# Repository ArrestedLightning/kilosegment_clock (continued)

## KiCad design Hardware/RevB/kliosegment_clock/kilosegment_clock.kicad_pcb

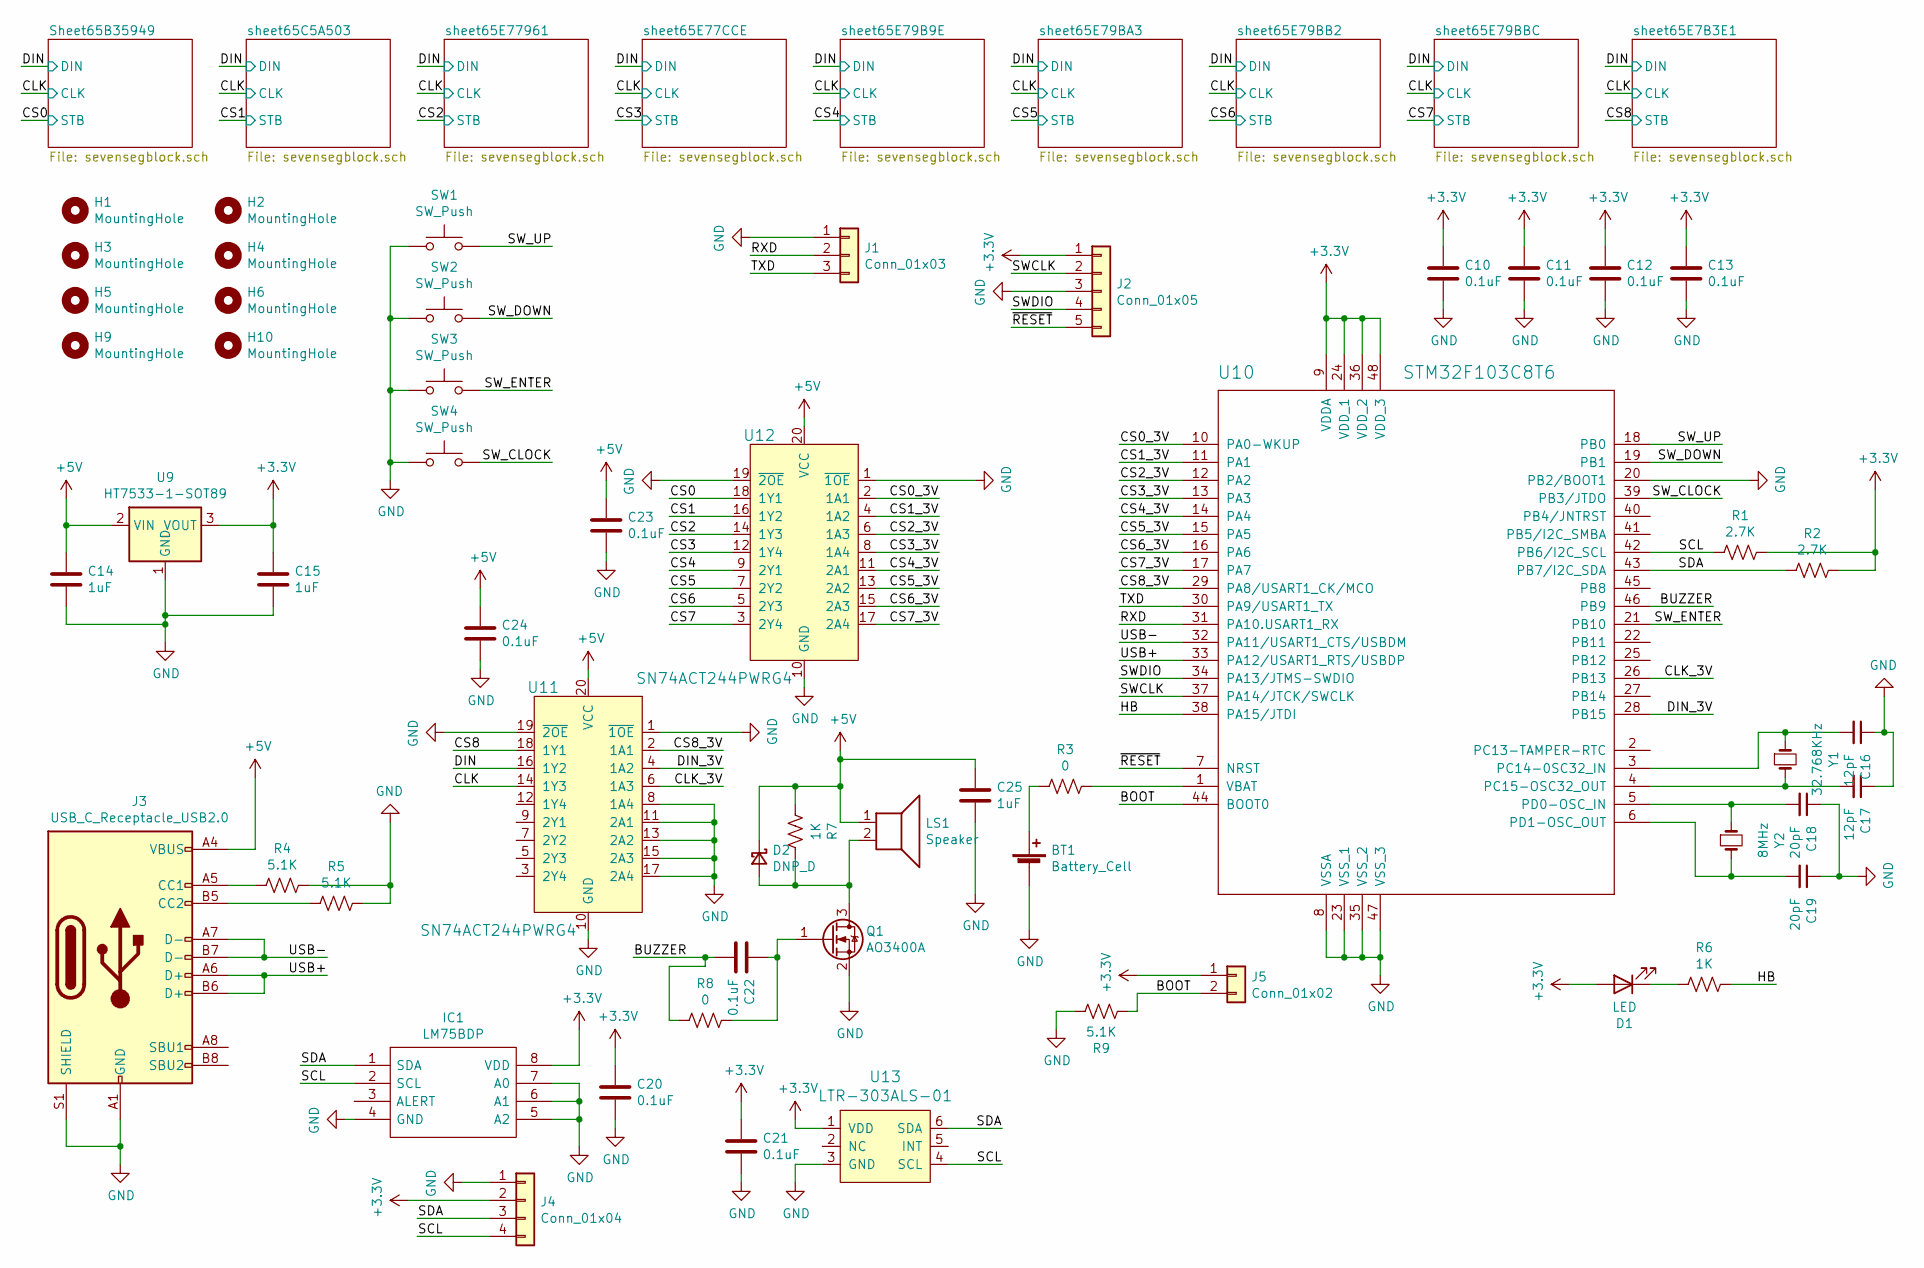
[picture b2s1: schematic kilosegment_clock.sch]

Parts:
BT1: Battery_Cell; BatteryHolder_CR2032-BS-6-1_1x2032; Digikey BH-49A-5-T-BK
C10, C11, C12, C13, C20, C21, C22, C23, C24: 0.1uF; C_0805_2012Metric_Pad1.18x1.45mm_HandSolder; Digikey 1276-1003-1-ND
C14, C15, C25: 1uF; C_0805_2012Metric_Pad1.18x1.45mm_HandSolder; Digikey 1276-1026-1-ND
C16, C17: 12pF; C_0805_2012Metric_Pad1.18x1.45mm_HandSolder; Digikey CML0805C0G120JT50V
C18, C19: 20pF; C_0805_2012Metric_Pad1.18x1.45mm_HandSolder; Digikey 738-CML0805C0G200JT50VCT-ND
D1: LED; LED_0805_2012Metric_Pad1.15x1.40mm_HandSolder; Digikey 754-1132-1-ND
D2: DNP_D; D_SOD-123
H1, H2, H3, H4, H5, H6, H9, H10: MountingHole; pcb_nut_m3
IC1: LM75BDP; MSOP-8_3x3mm_P0.65mm; Digikey 568-4768-1-ND
J1: Conn_01x03; PinHeader_1x03_P2.54mm_Vertical
J2: Conn_01x05; PinHeader_1x05_P2.54mm_Vertical
J3: USB_C_Receptacle_USB2.0; USB_C_Receptacle_HRO_TYPE-C-31-M-12; Digikey 664-12402012E212ACT-ND
J4: Conn_01x04; PinHeader_1x04_P2.54mm_Vertical
J5: Conn_01x02; PinHeader_1x02_P2.54mm_Vertical
LS1: Speaker; BUZ-TH_PKM13EPYH4002-B0; Digikey 490-4697-ND
Q1: AO3400A; SOT-23_Handsoldering; LCSC Part C20917
R1, R2: 2.7K; R_0805_2012Metric_Pad1.20x1.40mm_HandSolder; Digikey RMCF0805FT2K70CT-ND
R3, R8: 0; R_0805_2012Metric_Pad1.20x1.40mm_HandSolder; Digikey RMCF0805ZT0R00CT-ND
R4, R5, R9: 5.1K; R_0805_2012Metric_Pad1.20x1.40mm_HandSolder; Digikey RMCF0805FT5K10CT-ND
R6, R7: 1K; R_0805_2012Metric_Pad1.20x1.40mm_HandSolder; Digikey RMCF0805FT1K00CT-ND
SW1, SW2, SW3, SW4: SW_Push; SW_SPST_TL3342; Digikey CKN12222-1-ND
U9: HT7533-1-SOT89; SOT-89-3; Digikey 2129-RH5RL33AA-T1-FECT-ND
U10: STM32F103C8T6; LQFP-48_7x7mm_P0.5mm; Digikey 497-11517-ND
U11, U12: SN74ACT244PWRG4; TSSOP-20_4.4x6.5mm_P0.65mm; LCSC Part C6930
U13: LTR-303ALS-01; SOT-363_SC-70-6_Handsoldering; LCSC Part C364577
Y1: 32.768KHz; Crystal_SMD_3215-2Pin_3.2x1.5mm; Digikey 9H03200031-ND
Y2: 8MHz; Crystal_SMD_5032-2Pin_5.0x3.2mm_HandSoldering; Digikey XC2103CT-ND

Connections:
+3V3: C10.1, C11.1, C12.1, C13.1, C15.1, C20.1, C21.1, D1.2 (A), IC1.8 (VDD), J2.1, J4.2, J5.1, R1.1, R2.1, U9.3 (VOUT), U10.9 (VDDA), U10.24 (VDD_1), U10.36 (VDD_2), U10.48 (VDD_3), U13.1 (VDD)
+5V: C14.1, C23.1, C24.1, C25.1, D2.1 (K), J3.A4 (VBUS), J3.A9 (VBUS), J3.B4 (VBUS), J3.B9 (VBUS), LS1.1, R7.2, U9.2 (VIN), U11.20 (VCC), U12.20 (VCC); also elsewhere on the board
/BOOT: J5.2, R9.2, U10.44 (BOOT0)
/BUZZER: C22.2, R8.2, U10.46 (PB9)
/CLK: U11.14 (1Y3); also elsewhere on the board
/CLK_3V: U10.26 (PB13), U11.6 (1A3)
/CS0: U12.18 (1Y1); also elsewhere on the board
/CS0_3V: U10.10 (PA0-WKUP), U12.2 (1A1)
/CS1: U12.16 (1Y2); also elsewhere on the board
/CS1_3V: U10.11 (PA1), U12.4 (1A2)
/CS2: U12.14 (1Y3); also elsewhere on the board
/CS2_3V: U10.12 (PA2), U12.6 (1A3)
/CS3: U12.12 (1Y4); also elsewhere on the board
/CS3_3V: U10.13 (PA3), U12.8 (1A4)
/CS4: U12.9 (2Y1); also elsewhere on the board
/CS4_3V: U10.14 (PA4), U12.11 (2A1)
/CS5: U12.7 (2Y2); also elsewhere on the board
/CS5_3V: U10.15 (PA5), U12.13 (2A2)
/CS6: U12.5 (2Y3); also elsewhere on the board
/CS6_3V: U10.16 (PA6), U12.15 (2A3)
/CS7: U12.3 (2Y4); also elsewhere on the board
/CS7_3V: U10.17 (PA7), U12.17 (2A4)
/CS8: U11.18 (1Y1); also elsewhere on the board
/CS8_3V: U10.29 (PA8/USART1_CK/MCO), U11.2 (1A1)
/DIN: U11.16 (1Y2); also elsewhere on the board
/DIN_3V: U10.28 (PB15), U11.4 (1A2)
/HB: R6.1, U10.38 (PA15/JTDI)
/RXD: J1.2, U10.31 (PA10.USART1_RX)
/SCL: IC1.2 (SCL), J4.4, R1.2, U10.42 (PB6/I2C_SCL), U13.4 (SCL)
/SDA: IC1.1 (SDA), J4.3, R2.2, U10.43 (PB7/I2C_SDA), U13.6 (SDA)
/SWCLK: J2.2, U10.37 (PA14/JTCK/SWCLK)
/SWDIO: J2.4, U10.34 (PA13/JTMS-SWDIO)
/SW_CLOCK: SW4.2, U10.39 (PB3/JTDO)
/SW_DOWN: SW2.2, U10.19 (PB1)
/SW_ENTER: SW3.2, U10.21 (PB10)
/SW_UP: SW1.2, U10.18 (PB0)
/TXD: J1.3, U10.30 (PA9/USART1_TX)
/USB+: J3.A6 (D+), J3.B6 (D+), U10.33 (PA12/USART1_RTS/USBDP)
/USB-: J3.A7 (D-), J3.B7 (D-), U10.32 (PA11/USART1_CTS/USBDM)
/~RESET: J2.5, U10.7 (NRST)
GND: BT1.2 (-), C10.2, C11.2, C12.2, C13.2, C14.2, C15.2, C16.1, C17.1, C18.1, C19.1, C20.2, C21.2, C23.2, C24.2, C25.2, IC1.4 (GND), IC1.5 (A2), IC1.6 (A1), IC1.7 (A0), J1.1, J2.3, J3.A1 (GND), J3.A12 (GND), J3.B1 (GND), J3.B12 (GND), J3.S1 (SHIELD), J4.1, Q1.2 (S), R4.1, R5.1, R9.1, SW1.1, SW2.1, SW3.1, SW4.1, U9.1 (GND), U10.8 (VSSA), U10.20 (PB2/BOOT1), U10.23 (VSS_1), U10.35 (VSS_2), U10.47 (VSS_3), U11.1 (~1OE), U11.8 (1A4), U11.10 (GND), U11.11 (2A1), U11.13 (2A2), U11.15 (2A3), U11.17 (2A4), U11.19 (~2OE), U12.1 (~1OE), U12.10 (GND), U12.19 (~2OE), U13.3 (GND); also elsewhere on the board
unnamed: BT1.1 (+), R3.2
unnamed: C16.2, U10.3 (PC14-0SC32_IN), Y1.1
unnamed: C17.2, U10.4 (PC15-OSC32_OUT), Y1.2
unnamed: C18.2, U10.5 (PD0-OSC_IN), Y2.1
unnamed: C19.2, U10.6 (PD1-OSC_OUT), Y2.2
unnamed: C22.1, Q1.1 (G), R8.1
unnamed: D1.1 (K), R6.2
unnamed: D2.2 (A), LS1.2, Q1.3 (D), R7.1
unnamed: J3.A5 (CC1), R4.2
unnamed: J3.B5 (CC2), R5.2
unnamed: R3.1, U10.1 (VBAT)

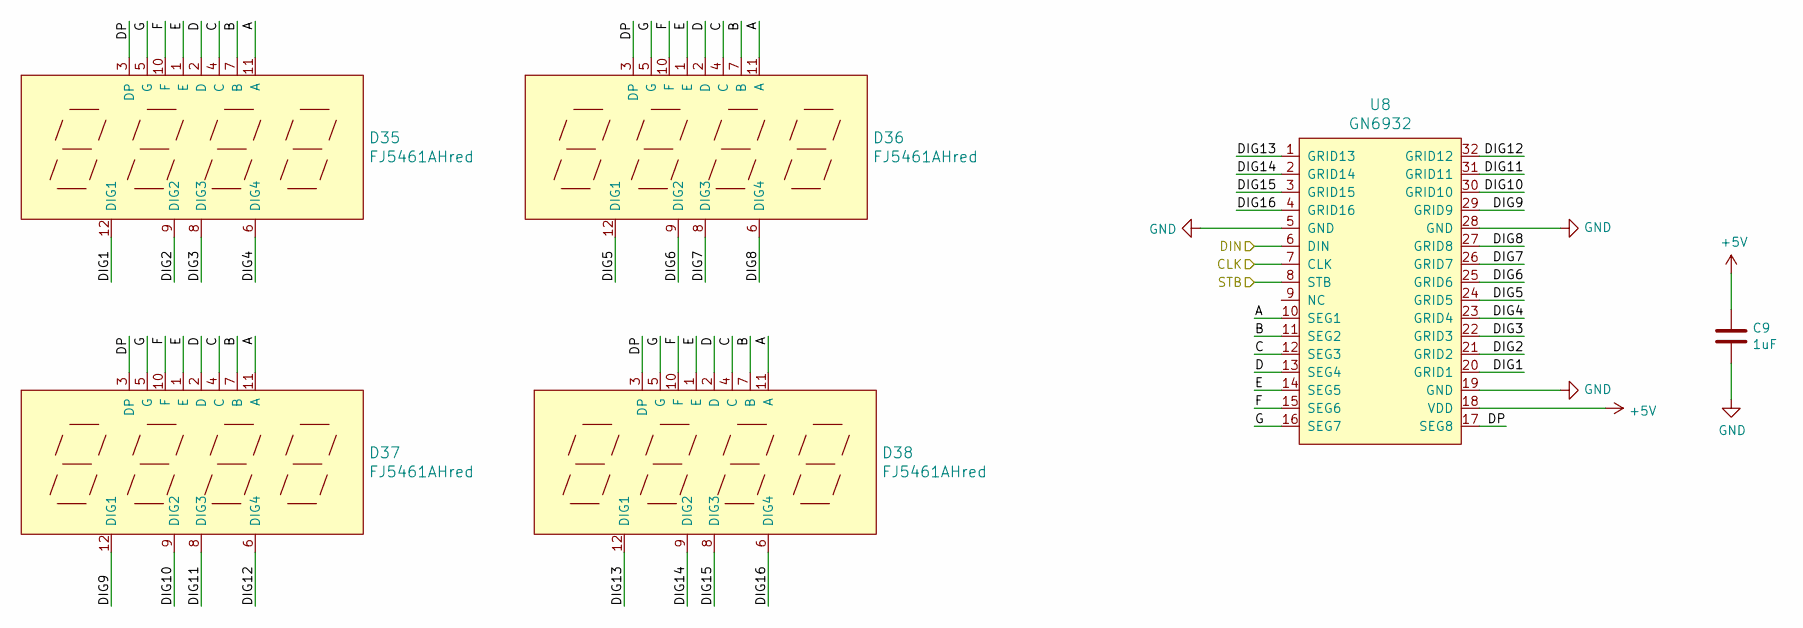
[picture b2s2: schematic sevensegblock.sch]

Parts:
C1: 1uF; C_0805_2012Metric_Pad1.18x1.45mm_HandSolder; Digikey 1276-1026-1-ND
D3, D4, D5, D6: FJ5461AHred; LED-SEG-TH_FJ5461AH; LCSC Part C54396
U0: GN6932; SOP-32_L21.0-W7.5-P1.27-LS10.4-BL; LCSC Part C265476

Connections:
+5V: C1.1, U0.18 (VDD); also elsewhere on the board
/CLK: U0.7 (CLK); also elsewhere on the board
/CS0: U0.8 (STB); also elsewhere on the board
/DIN: U0.6 (DIN); also elsewhere on the board
/Sheet65B35949/A: D3.11 (A), D4.11 (A), D5.11 (A), D6.11 (A), U0.10 (SEG1)
/Sheet65B35949/B: D3.7 (B), D4.7 (B), D5.7 (B), D6.7 (B), U0.11 (SEG2)
/Sheet65B35949/C: D3.4 (C), D4.4 (C), D5.4 (C), D6.4 (C), U0.12 (SEG3)
/Sheet65B35949/D: D3.2 (D), D4.2 (D), D5.2 (D), D6.2 (D), U0.13 (SEG4)
/Sheet65B35949/DIG1: D3.12 (DIG1), U0.20 (GRID1)
/Sheet65B35949/DIG2: D3.9 (DIG2), U0.21 (GRID2)
/Sheet65B35949/DIG3: D3.8 (DIG3), U0.22 (GRID3)
/Sheet65B35949/DIG4: D3.6 (DIG4), U0.23 (GRID4)
/Sheet65B35949/DIG5: D4.12 (DIG1), U0.24 (GRID5)
/Sheet65B35949/DIG6: D4.9 (DIG2), U0.25 (GRID6)
/Sheet65B35949/DIG7: D4.8 (DIG3), U0.26 (GRID7)
/Sheet65B35949/DIG8: D4.6 (DIG4), U0.27 (GRID8)
/Sheet65B35949/DIG9: D5.12 (DIG1), U0.29 (GRID9)
/Sheet65B35949/DIG10: D5.9 (DIG2), U0.30 (GRID10)
/Sheet65B35949/DIG11: D5.8 (DIG3), U0.31 (GRID11)
/Sheet65B35949/DIG12: D5.6 (DIG4), U0.32 (GRID12)
/Sheet65B35949/DIG13: D6.12 (DIG1), U0.1 (GRID13)
/Sheet65B35949/DIG14: D6.9 (DIG2), U0.2 (GRID14)
/Sheet65B35949/DIG15: D6.8 (DIG3), U0.3 (GRID15)
/Sheet65B35949/DIG16: D6.6 (DIG4), U0.4 (GRID16)
/Sheet65B35949/DP: D3.3 (DP), D4.3 (DP), D5.3 (DP), D6.3 (DP), U0.17 (SEG8)
/Sheet65B35949/E: D3.1 (E), D4.1 (E), D5.1 (E), D6.1 (E), U0.14 (SEG5)
/Sheet65B35949/F: D3.10 (F), D4.10 (F), D5.10 (F), D6.10 (F), U0.15 (SEG6)
/Sheet65B35949/G: D3.5 (G), D4.5 (G), D5.5 (G), D6.5 (G), U0.16 (SEG7)
GND: C1.2, U0.5 (GND), U0.19 (GND), U0.28 (GND); also elsewhere on the board

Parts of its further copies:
C2, C3, C4, C5, C6, C7, C8, C9: 1uF; C_0805_2012Metric_Pad1.18x1.45mm_HandSolder; Digikey 1276-1026-1-ND
D7, D8, D9, D10, D11, D12, D13, D14, D15, D16, D17, D18, D19, D20, D21, D22, D23, D24, D25, D26, D27, D28, D29, D30, D31, D32, D33, D34, D35, D36, D37, D38: FJ5461AHred; LED-SEG-TH_FJ5461AH; LCSC Part C54396
U1, U2, U3, U4, U5, U6, U7, U8: GN6932; SOP-32_L21.0-W7.5-P1.27-LS10.4-BL; LCSC Part C265476

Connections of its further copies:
+5V: C2.1, C3.1, C4.1, C5.1, C6.1, C7.1, C8.1, C9.1, U1.18 (VDD), U2.18 (VDD), U3.18 (VDD), U4.18 (VDD), U5.18 (VDD), U6.18 (VDD), U7.18 (VDD), U8.18 (VDD); also elsewhere on the board
/CLK: U1.7 (CLK), U2.7 (CLK), U3.7 (CLK), U4.7 (CLK), U5.7 (CLK), U6.7 (CLK), U7.7 (CLK), U8.7 (CLK); also elsewhere on the board
/CS1: U1.8 (STB); also elsewhere on the board
/CS2: U2.8 (STB); also elsewhere on the board
/CS3: U3.8 (STB); also elsewhere on the board
/CS4: U4.8 (STB); also elsewhere on the board
/CS5: U5.8 (STB); also elsewhere on the board
/CS6: U6.8 (STB); also elsewhere on the board
/CS7: U7.8 (STB); also elsewhere on the board
/CS8: U8.8 (STB); also elsewhere on the board
/DIN: U1.6 (DIN), U2.6 (DIN), U3.6 (DIN), U4.6 (DIN), U5.6 (DIN), U6.6 (DIN), U7.6 (DIN), U8.6 (DIN); also elsewhere on the board
/sheet65C5A503/A: D7.11 (A), D8.11 (A), D9.11 (A), D10.11 (A), U1.10 (SEG1)
/sheet65C5A503/B: D7.7 (B), D8.7 (B), D9.7 (B), D10.7 (B), U1.11 (SEG2)
/sheet65C5A503/C: D7.4 (C), D8.4 (C), D9.4 (C), D10.4 (C), U1.12 (SEG3)
/sheet65C5A503/D: D7.2 (D), D8.2 (D), D9.2 (D), D10.2 (D), U1.13 (SEG4)
/sheet65C5A503/DIG1: D7.12 (DIG1), U1.20 (GRID1)
/sheet65C5A503/DIG2: D7.9 (DIG2), U1.21 (GRID2)
/sheet65C5A503/DIG3: D7.8 (DIG3), U1.22 (GRID3)
/sheet65C5A503/DIG4: D7.6 (DIG4), U1.23 (GRID4)
/sheet65C5A503/DIG5: D8.12 (DIG1), U1.24 (GRID5)
/sheet65C5A503/DIG6: D8.9 (DIG2), U1.25 (GRID6)
/sheet65C5A503/DIG7: D8.8 (DIG3), U1.26 (GRID7)
/sheet65C5A503/DIG8: D8.6 (DIG4), U1.27 (GRID8)
/sheet65C5A503/DIG9: D9.12 (DIG1), U1.29 (GRID9)
/sheet65C5A503/DIG10: D9.9 (DIG2), U1.30 (GRID10)
/sheet65C5A503/DIG11: D9.8 (DIG3), U1.31 (GRID11)
/sheet65C5A503/DIG12: D9.6 (DIG4), U1.32 (GRID12)
/sheet65C5A503/DIG13: D10.12 (DIG1), U1.1 (GRID13)
/sheet65C5A503/DIG14: D10.9 (DIG2), U1.2 (GRID14)
/sheet65C5A503/DIG15: D10.8 (DIG3), U1.3 (GRID15)
/sheet65C5A503/DIG16: D10.6 (DIG4), U1.4 (GRID16)
/sheet65C5A503/DP: D7.3 (DP), D8.3 (DP), D9.3 (DP), D10.3 (DP), U1.17 (SEG8)
/sheet65C5A503/E: D7.1 (E), D8.1 (E), D9.1 (E), D10.1 (E), U1.14 (SEG5)
/sheet65C5A503/F: D7.10 (F), D8.10 (F), D9.10 (F), D10.10 (F), U1.15 (SEG6)
/sheet65C5A503/G: D7.5 (G), D8.5 (G), D9.5 (G), D10.5 (G), U1.16 (SEG7)
/sheet65E7B3E1/A: D35.11 (A), D36.11 (A), D37.11 (A), D38.11 (A), U8.10 (SEG1)
/sheet65E7B3E1/B: D35.7 (B), D36.7 (B), D37.7 (B), D38.7 (B), U8.11 (SEG2)
/sheet65E7B3E1/C: D35.4 (C), D36.4 (C), D37.4 (C), D38.4 (C), U8.12 (SEG3)
/sheet65E7B3E1/D: D35.2 (D), D36.2 (D), D37.2 (D), D38.2 (D), U8.13 (SEG4)
/sheet65E7B3E1/DIG1: D35.12 (DIG1), U8.20 (GRID1)
/sheet65E7B3E1/DIG2: D35.9 (DIG2), U8.21 (GRID2)
/sheet65E7B3E1/DIG3: D35.8 (DIG3), U8.22 (GRID3)
/sheet65E7B3E1/DIG4: D35.6 (DIG4), U8.23 (GRID4)
/sheet65E7B3E1/DIG5: D36.12 (DIG1), U8.24 (GRID5)
/sheet65E7B3E1/DIG6: D36.9 (DIG2), U8.25 (GRID6)
/sheet65E7B3E1/DIG7: D36.8 (DIG3), U8.26 (GRID7)
/sheet65E7B3E1/DIG8: D36.6 (DIG4), U8.27 (GRID8)
/sheet65E7B3E1/DIG9: D37.12 (DIG1), U8.29 (GRID9)
/sheet65E7B3E1/DIG10: D37.9 (DIG2), U8.30 (GRID10)
/sheet65E7B3E1/DIG11: D37.8 (DIG3), U8.31 (GRID11)
/sheet65E7B3E1/DIG12: D37.6 (DIG4), U8.32 (GRID12)
/sheet65E7B3E1/DIG13: D38.12 (DIG1), U8.1 (GRID13)
/sheet65E7B3E1/DIG14: D38.9 (DIG2), U8.2 (GRID14)
/sheet65E7B3E1/DIG15: D38.8 (DIG3), U8.3 (GRID15)
/sheet65E7B3E1/DIG16: D38.6 (DIG4), U8.4 (GRID16)
/sheet65E7B3E1/DP: D35.3 (DP), D36.3 (DP), D37.3 (DP), D38.3 (DP), U8.17 (SEG8)
/sheet65E7B3E1/E: D35.1 (E), D36.1 (E), D37.1 (E), D38.1 (E), U8.14 (SEG5)
/sheet65E7B3E1/F: D35.10 (F), D36.10 (F), D37.10 (F), D38.10 (F), U8.15 (SEG6)
/sheet65E7B3E1/G: D35.5 (G), D36.5 (G), D37.5 (G), D38.5 (G), U8.16 (SEG7)
/sheet65E77CCE/A: D15.11 (A), D16.11 (A), D17.11 (A), D18.11 (A), U3.10 (SEG1)
/sheet65E77CCE/B: D15.7 (B), D16.7 (B), D17.7 (B), D18.7 (B), U3.11 (SEG2)
/sheet65E77CCE/C: D15.4 (C), D16.4 (C), D17.4 (C), D18.4 (C), U3.12 (SEG3)
/sheet65E77CCE/D: D15.2 (D), D16.2 (D), D17.2 (D), D18.2 (D), U3.13 (SEG4)
/sheet65E77CCE/DIG1: D15.12 (DIG1), U3.20 (GRID1)
/sheet65E77CCE/DIG2: D15.9 (DIG2), U3.21 (GRID2)
/sheet65E77CCE/DIG3: D15.8 (DIG3), U3.22 (GRID3)
/sheet65E77CCE/DIG4: D15.6 (DIG4), U3.23 (GRID4)
/sheet65E77CCE/DIG5: D16.12 (DIG1), U3.24 (GRID5)
/sheet65E77CCE/DIG6: D16.9 (DIG2), U3.25 (GRID6)
/sheet65E77CCE/DIG7: D16.8 (DIG3), U3.26 (GRID7)
/sheet65E77CCE/DIG8: D16.6 (DIG4), U3.27 (GRID8)
/sheet65E77CCE/DIG9: D17.12 (DIG1), U3.29 (GRID9)
/sheet65E77CCE/DIG10: D17.9 (DIG2), U3.30 (GRID10)
/sheet65E77CCE/DIG11: D17.8 (DIG3), U3.31 (GRID11)
/sheet65E77CCE/DIG12: D17.6 (DIG4), U3.32 (GRID12)
/sheet65E77CCE/DIG13: D18.12 (DIG1), U3.1 (GRID13)
/sheet65E77CCE/DIG14: D18.9 (DIG2), U3.2 (GRID14)
/sheet65E77CCE/DIG15: D18.8 (DIG3), U3.3 (GRID15)
/sheet65E77CCE/DIG16: D18.6 (DIG4), U3.4 (GRID16)
/sheet65E77CCE/DP: D15.3 (DP), D16.3 (DP), D17.3 (DP), D18.3 (DP), U3.17 (SEG8)
/sheet65E77CCE/E: D15.1 (E), D16.1 (E), D17.1 (E), D18.1 (E), U3.14 (SEG5)
/sheet65E77CCE/F: D15.10 (F), D16.10 (F), D17.10 (F), D18.10 (F), U3.15 (SEG6)
/sheet65E77CCE/G: D15.5 (G), D16.5 (G), D17.5 (G), D18.5 (G), U3.16 (SEG7)
/sheet65E79B9E/A: D19.11 (A), D20.11 (A), D21.11 (A), D22.11 (A), U4.10 (SEG1)
/sheet65E79B9E/B: D19.7 (B), D20.7 (B), D21.7 (B), D22.7 (B), U4.11 (SEG2)
/sheet65E79B9E/C: D19.4 (C), D20.4 (C), D21.4 (C), D22.4 (C), U4.12 (SEG3)
/sheet65E79B9E/D: D19.2 (D), D20.2 (D), D21.2 (D), D22.2 (D), U4.13 (SEG4)
/sheet65E79B9E/DIG1: D19.12 (DIG1), U4.20 (GRID1)
/sheet65E79B9E/DIG2: D19.9 (DIG2), U4.21 (GRID2)
/sheet65E79B9E/DIG3: D19.8 (DIG3), U4.22 (GRID3)
/sheet65E79B9E/DIG4: D19.6 (DIG4), U4.23 (GRID4)
/sheet65E79B9E/DIG5: D20.12 (DIG1), U4.24 (GRID5)
/sheet65E79B9E/DIG6: D20.9 (DIG2), U4.25 (GRID6)
/sheet65E79B9E/DIG7: D20.8 (DIG3), U4.26 (GRID7)
/sheet65E79B9E/DIG8: D20.6 (DIG4), U4.27 (GRID8)
/sheet65E79B9E/DIG9: D21.12 (DIG1), U4.29 (GRID9)
/sheet65E79B9E/DIG10: D21.9 (DIG2), U4.30 (GRID10)
/sheet65E79B9E/DIG11: D21.8 (DIG3), U4.31 (GRID11)
/sheet65E79B9E/DIG12: D21.6 (DIG4), U4.32 (GRID12)
/sheet65E79B9E/DIG13: D22.12 (DIG1), U4.1 (GRID13)
/sheet65E79B9E/DIG14: D22.9 (DIG2), U4.2 (GRID14)
/sheet65E79B9E/DIG15: D22.8 (DIG3), U4.3 (GRID15)
/sheet65E79B9E/DIG16: D22.6 (DIG4), U4.4 (GRID16)
/sheet65E79B9E/DP: D19.3 (DP), D20.3 (DP), D21.3 (DP), D22.3 (DP), U4.17 (SEG8)
/sheet65E79B9E/E: D19.1 (E), D20.1 (E), D21.1 (E), D22.1 (E), U4.14 (SEG5)
/sheet65E79B9E/F: D19.10 (F), D20.10 (F), D21.10 (F), D22.10 (F), U4.15 (SEG6)
/sheet65E79B9E/G: D19.5 (G), D20.5 (G), D21.5 (G), D22.5 (G), U4.16 (SEG7)
/sheet65E79BA3/A: D23.11 (A), D24.11 (A), D25.11 (A), D26.11 (A), U5.10 (SEG1)
/sheet65E79BA3/B: D23.7 (B), D24.7 (B), D25.7 (B), D26.7 (B), U5.11 (SEG2)
/sheet65E79BA3/C: D23.4 (C), D24.4 (C), D25.4 (C), D26.4 (C), U5.12 (SEG3)
/sheet65E79BA3/D: D23.2 (D), D24.2 (D), D25.2 (D), D26.2 (D), U5.13 (SEG4)
/sheet65E79BA3/DIG1: D23.12 (DIG1), U5.20 (GRID1)
/sheet65E79BA3/DIG2: D23.9 (DIG2), U5.21 (GRID2)
/sheet65E79BA3/DIG3: D23.8 (DIG3), U5.22 (GRID3)
/sheet65E79BA3/DIG4: D23.6 (DIG4), U5.23 (GRID4)
/sheet65E79BA3/DIG5: D24.12 (DIG1), U5.24 (GRID5)
/sheet65E79BA3/DIG6: D24.9 (DIG2), U5.25 (GRID6)
/sheet65E79BA3/DIG7: D24.8 (DIG3), U5.26 (GRID7)
/sheet65E79BA3/DIG8: D24.6 (DIG4), U5.27 (GRID8)
/sheet65E79BA3/DIG9: D25.12 (DIG1), U5.29 (GRID9)
/sheet65E79BA3/DIG10: D25.9 (DIG2), U5.30 (GRID10)
/sheet65E79BA3/DIG11: D25.8 (DIG3), U5.31 (GRID11)
/sheet65E79BA3/DIG12: D25.6 (DIG4), U5.32 (GRID12)
/sheet65E79BA3/DIG13: D26.12 (DIG1), U5.1 (GRID13)
/sheet65E79BA3/DIG14: D26.9 (DIG2), U5.2 (GRID14)
/sheet65E79BA3/DIG15: D26.8 (DIG3), U5.3 (GRID15)
/sheet65E79BA3/DIG16: D26.6 (DIG4), U5.4 (GRID16)
/sheet65E79BA3/DP: D23.3 (DP), D24.3 (DP), D25.3 (DP), D26.3 (DP), U5.17 (SEG8)
/sheet65E79BA3/E: D23.1 (E), D24.1 (E), D25.1 (E), D26.1 (E), U5.14 (SEG5)
/sheet65E79BA3/F: D23.10 (F), D24.10 (F), D25.10 (F), D26.10 (F), U5.15 (SEG6)
/sheet65E79BA3/G: D23.5 (G), D24.5 (G), D25.5 (G), D26.5 (G), U5.16 (SEG7)
/sheet65E79BB2/A: D27.11 (A), D28.11 (A), D29.11 (A), D30.11 (A), U6.10 (SEG1)
/sheet65E79BB2/B: D27.7 (B), D28.7 (B), D29.7 (B), D30.7 (B), U6.11 (SEG2)
/sheet65E79BB2/C: D27.4 (C), D28.4 (C), D29.4 (C), D30.4 (C), U6.12 (SEG3)
/sheet65E79BB2/D: D27.2 (D), D28.2 (D), D29.2 (D), D30.2 (D), U6.13 (SEG4)
/sheet65E79BB2/DIG1: D27.12 (DIG1), U6.20 (GRID1)
/sheet65E79BB2/DIG2: D27.9 (DIG2), U6.21 (GRID2)
/sheet65E79BB2/DIG3: D27.8 (DIG3), U6.22 (GRID3)
/sheet65E79BB2/DIG4: D27.6 (DIG4), U6.23 (GRID4)
/sheet65E79BB2/DIG5: D28.12 (DIG1), U6.24 (GRID5)
/sheet65E79BB2/DIG6: D28.9 (DIG2), U6.25 (GRID6)
/sheet65E79BB2/DIG7: D28.8 (DIG3), U6.26 (GRID7)
/sheet65E79BB2/DIG8: D28.6 (DIG4), U6.27 (GRID8)
/sheet65E79BB2/DIG9: D29.12 (DIG1), U6.29 (GRID9)
/sheet65E79BB2/DIG10: D29.9 (DIG2), U6.30 (GRID10)
/sheet65E79BB2/DIG11: D29.8 (DIG3), U6.31 (GRID11)
/sheet65E79BB2/DIG12: D29.6 (DIG4), U6.32 (GRID12)
/sheet65E79BB2/DIG13: D30.12 (DIG1), U6.1 (GRID13)
/sheet65E79BB2/DIG14: D30.9 (DIG2), U6.2 (GRID14)
/sheet65E79BB2/DIG15: D30.8 (DIG3), U6.3 (GRID15)
/sheet65E79BB2/DIG16: D30.6 (DIG4), U6.4 (GRID16)
/sheet65E79BB2/DP: D27.3 (DP), D28.3 (DP), D29.3 (DP), D30.3 (DP), U6.17 (SEG8)
/sheet65E79BB2/E: D27.1 (E), D28.1 (E), D29.1 (E), D30.1 (E), U6.14 (SEG5)
/sheet65E79BB2/F: D27.10 (F), D28.10 (F), D29.10 (F), D30.10 (F), U6.15 (SEG6)
/sheet65E79BB2/G: D27.5 (G), D28.5 (G), D29.5 (G), D30.5 (G), U6.16 (SEG7)
/sheet65E79BBC/A: D31.11 (A), D32.11 (A), D33.11 (A), D34.11 (A), U7.10 (SEG1)
/sheet65E79BBC/B: D31.7 (B), D32.7 (B), D33.7 (B), D34.7 (B), U7.11 (SEG2)
/sheet65E79BBC/C: D31.4 (C), D32.4 (C), D33.4 (C), D34.4 (C), U7.12 (SEG3)
/sheet65E79BBC/D: D31.2 (D), D32.2 (D), D33.2 (D), D34.2 (D), U7.13 (SEG4)
/sheet65E79BBC/DIG1: D31.12 (DIG1), U7.20 (GRID1)
/sheet65E79BBC/DIG2: D31.9 (DIG2), U7.21 (GRID2)
/sheet65E79BBC/DIG3: D31.8 (DIG3), U7.22 (GRID3)
/sheet65E79BBC/DIG4: D31.6 (DIG4), U7.23 (GRID4)
/sheet65E79BBC/DIG5: D32.12 (DIG1), U7.24 (GRID5)
/sheet65E79BBC/DIG6: D32.9 (DIG2), U7.25 (GRID6)
/sheet65E79BBC/DIG7: D32.8 (DIG3), U7.26 (GRID7)
/sheet65E79BBC/DIG8: D32.6 (DIG4), U7.27 (GRID8)
/sheet65E79BBC/DIG9: D33.12 (DIG1), U7.29 (GRID9)
/sheet65E79BBC/DIG10: D33.9 (DIG2), U7.30 (GRID10)
/sheet65E79BBC/DIG11: D33.8 (DIG3), U7.31 (GRID11)
/sheet65E79BBC/DIG12: D33.6 (DIG4), U7.32 (GRID12)
/sheet65E79BBC/DIG13: D34.12 (DIG1), U7.1 (GRID13)
/sheet65E79BBC/DIG14: D34.9 (DIG2), U7.2 (GRID14)
/sheet65E79BBC/DIG15: D34.8 (DIG3), U7.3 (GRID15)
/sheet65E79BBC/DIG16: D34.6 (DIG4), U7.4 (GRID16)
/sheet65E79BBC/DP: D31.3 (DP), D32.3 (DP), D33.3 (DP), D34.3 (DP), U7.17 (SEG8)
/sheet65E79BBC/E: D31.1 (E), D32.1 (E), D33.1 (E), D34.1 (E), U7.14 (SEG5)
/sheet65E79BBC/F: D31.10 (F), D32.10 (F), D33.10 (F), D34.10 (F), U7.15 (SEG6)
/sheet65E79BBC/G: D31.5 (G), D32.5 (G), D33.5 (G), D34.5 (G), U7.16 (SEG7)
/sheet65E77961/A: D11.11 (A), D12.11 (A), D13.11 (A), D14.11 (A), U2.10 (SEG1)
/sheet65E77961/B: D11.7 (B), D12.7 (B), D13.7 (B), D14.7 (B), U2.11 (SEG2)
/sheet65E77961/C: D11.4 (C), D12.4 (C), D13.4 (C), D14.4 (C), U2.12 (SEG3)
/sheet65E77961/D: D11.2 (D), D12.2 (D), D13.2 (D), D14.2 (D), U2.13 (SEG4)
/sheet65E77961/DIG1: D11.12 (DIG1), U2.20 (GRID1)
/sheet65E77961/DIG2: D11.9 (DIG2), U2.21 (GRID2)
/sheet65E77961/DIG3: D11.8 (DIG3), U2.22 (GRID3)
/sheet65E77961/DIG4: D11.6 (DIG4), U2.23 (GRID4)
/sheet65E77961/DIG5: D12.12 (DIG1), U2.24 (GRID5)
/sheet65E77961/DIG6: D12.9 (DIG2), U2.25 (GRID6)
/sheet65E77961/DIG7: D12.8 (DIG3), U2.26 (GRID7)
/sheet65E77961/DIG8: D12.6 (DIG4), U2.27 (GRID8)
/sheet65E77961/DIG9: D13.12 (DIG1), U2.29 (GRID9)
/sheet65E77961/DIG10: D13.9 (DIG2), U2.30 (GRID10)
/sheet65E77961/DIG11: D13.8 (DIG3), U2.31 (GRID11)
/sheet65E77961/DIG12: D13.6 (DIG4), U2.32 (GRID12)
/sheet65E77961/DIG13: D14.12 (DIG1), U2.1 (GRID13)
/sheet65E77961/DIG14: D14.9 (DIG2), U2.2 (GRID14)
/sheet65E77961/DIG15: D14.8 (DIG3), U2.3 (GRID15)
/sheet65E77961/DIG16: D14.6 (DIG4), U2.4 (GRID16)
/sheet65E77961/DP: D11.3 (DP), D12.3 (DP), D13.3 (DP), D14.3 (DP), U2.17 (SEG8)
/sheet65E77961/E: D11.1 (E), D12.1 (E), D13.1 (E), D14.1 (E), U2.14 (SEG5)
/sheet65E77961/F: D11.10 (F), D12.10 (F), D13.10 (F), D14.10 (F), U2.15 (SEG6)
/sheet65E77961/G: D11.5 (G), D12.5 (G), D13.5 (G), D14.5 (G), U2.16 (SEG7)
GND: C2.2, C3.2, C4.2, C5.2, C6.2, C7.2, C8.2, C9.2, U1.5 (GND), U1.19 (GND), U1.28 (GND), U2.5 (GND), U2.19 (GND), U2.28 (GND), U3.5 (GND), U3.19 (GND), U3.28 (GND), U4.5 (GND), U4.19 (GND), U4.28 (GND), U5.5 (GND), U5.19 (GND), U5.28 (GND), U6.5 (GND), U6.19 (GND), U6.28 (GND), U7.5 (GND), U7.19 (GND), U7.28 (GND), U8.5 (GND), U8.19 (GND), U8.28 (GND); also elsewhere on the board

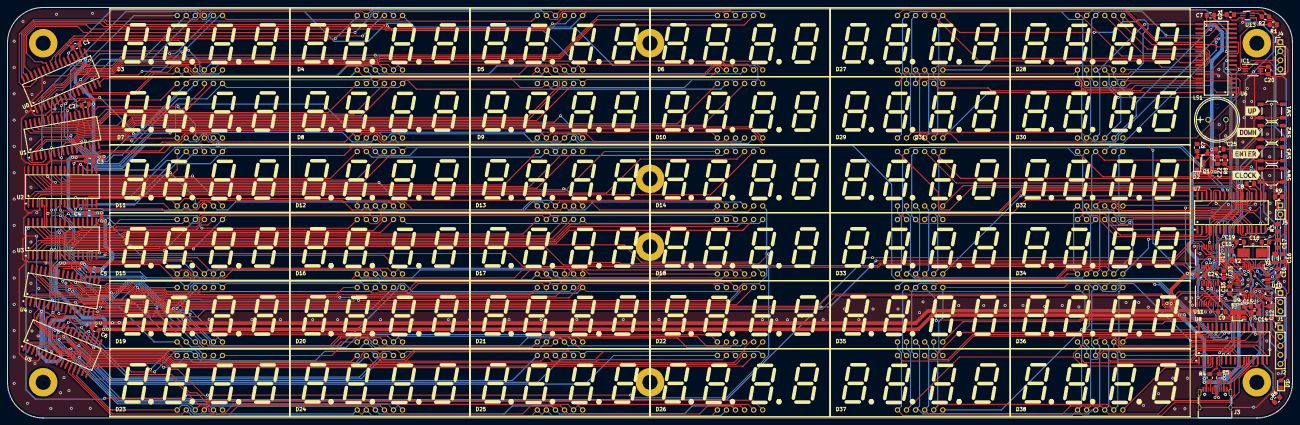
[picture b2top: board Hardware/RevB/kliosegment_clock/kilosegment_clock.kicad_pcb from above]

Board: 2 copper layers, 360.0 x 115.0 mm, 113 parts (1 on the bottom side), 268 nets.

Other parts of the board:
kibuzzard-6249F0CC, kibuzzard-6249F13F, kibuzzard-6249F15D, kibuzzard-6249F086: G***; label

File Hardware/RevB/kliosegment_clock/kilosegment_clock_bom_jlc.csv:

"Comment","Designator","Footprint","LCSC Part #"
"Battery_Cell","BT1","BatteryHolder_CR2032-BS-6-1_1x2032","C964764"
"0.1uF","C10,C11,C12,C13,C20,C21,C22,C24,C23","C_0805_2012Metric_Pad1.18x1.45mm_HandSolder","C49678"
"1uF","C14,C15,C25,C1,C2,C3,C4,C5,C6,C7,C8,C9","C_0805_2012Metric_Pad1.18x1.45mm_HandSolder","C28323"
"12pF","C16,C17","C_0805_2012Metric_Pad1.18x1.45mm_HandSolder","C1792"
"20pF","C18,C19","C_0805_2012Metric_Pad1.18x1.45mm_HandSolder","C1798"
"LED","D1","LED_0805_2012Metric_Pad1.15x1.40mm_HandSolder","C84256"
"FJ5461AHred","D6,D5,D4,D3,D10,D9,D8,D7,D14,D13,D12,D11,D18,D17,D16,D15,D22,D21,D20,D19,D26,D25,D24,D23,D30,D29,D28,D27,D34,D33,D32,D31,D38,D37,D36,D35","LED-SEG-TH_FJ5461AH","C54396"
"LM75BDP","IC1","MSOP-8_3x3mm_P0.65mm","C2837470"
"USB_C_Receptacle_USB2.0","J3","USB_C_Receptacle_HRO_TYPE-C-31-M-12","C165948"
"Speaker","LS1","BUZ-TH_PKM13EPYH4002-B0","C128650"
"AO3400A","Q1","SOT-23_Handsoldering","C20917"
"2.7K","R1,R2","R_0805_2012Metric_Pad1.20x1.40mm_HandSolder","C17530"
"0","R3,R8","R_0805_2012Metric_Pad1.20x1.40mm_HandSolder","C17477"
"5.1K","R4,R5,R9","R_0805_2012Metric_Pad1.20x1.40mm_HandSolder","C27834"
"1K","R7,R6","R_0805_2012Metric_Pad1.20x1.40mm_HandSolder","C17513"
"SW_Push","SW1,SW2,SW3,SW4","SW_SPST_TL3342","C318886"
"GN6932","U0,U1,U2,U3,U4,U5,U6,U7,U8","SOP-32_L21.0-W7.5-P1.27-LS10.4-BL","C265476"
"HT7533-1-SOT89","U9","SOT-89-3","C14289"
"STM32F103C8T6","U10","LQFP-48_7x7mm_P0.5mm","C77994"
"SN74ACT244PWRG4","U12,U11","TSSOP-20_4.4x6.5mm_P0.65mm","C6930"
"LTR-303ALS-01","U13","SOT-363_SC-70-6_Handsoldering","C364577"
"32.768KHz","Y1","Crystal_SMD_3215-2Pin_3.2x1.5mm","C32346"
"8MHz","Y2","Crystal_SMD_5032-2Pin_5.0x3.2mm_HandSoldering","C115962"

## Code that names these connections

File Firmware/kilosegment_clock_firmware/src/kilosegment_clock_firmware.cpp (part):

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

/* Pin definitions */
#define LED_CLK   PB13
#define LED_DIN   PB14 //not used
#define LED_DOUT  PB15


#define SPEAKER   PB9
#define SW_UP     PB0
#define SW_DOWN   PB1
#define SW_ENTER  PB10
#define SW_CLOCK  PB3

#define HB_LED    PA15

#define NUM_DISPLAY_DRIVERS 9

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//Temporary time structure
TimeElements newTime = { 0 };

const uint32_t led_chip_select_pins[NUM_DISPLAY_DRIVERS] = { PA0, PA1, PA2, PA3, PA4, PA5, PA6, PA7, PA8 };
//display driver objects
xx6932 display_drivers[NUM_DISPLAY_DRIVERS];
//LED_DIN is not used, but provided here to keep the library happy
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
LTR303 light_sensor;

HardwareSerial Serial1(PA10, PA9);

static void cmd_print_help       (char *args, char *response, size_t response_len);
static void cmd_print_version    (char *args, char *response, size_t response_len);
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
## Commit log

2022-07-23 Initial commit with unmodified firmware
2022-07-27 Initial working firmware version on new hardware
2022-07-30 Temp sensor support, update ASCII table, change menu logic
2022-07-30 Auto-generate and include a build number and build date
2022-08-01 Working on debug mode; fixed year setting, rough implementation of auto-brightness
2022-08-01 Bring back the timeout on the date display screen
2022-08-01 Basic settings storage works. Not ideal due to lack of wear leveling.
2022-08-04 Use correct RTC library calls, fix set day, some EEPROM sanity checking
2022-08-28 Fix typo in file names
2022-08-28 Scale autobrightness max value to brightness configuration value
2022-08-28 Make AM/PM indicator and colon configurable. Show dot when alarm enabled.
2022-09-03 improve config storage reliability, show message when defaults are loaded, Replace log10 with integer function
2022-09-03 Added USB bootloader (not fully tested)
2022-09-03 Added acknowledgments to readme
2022-12-31 CLI (work in progress), 12 hour time format in settings
2022-12-31 Change square font to exclude decmal points, add beep alarm sounds
2023-03-19 Exit menu when clock button held down
2023-03-19 Added function to display date at specified intervals.
2023-06-27 non-blocking main loop, additional filtering on light sensor
2023-09-30 Add default cases to switch statements
2023-11-30 Implement a simple command-line interface. Add a workaround for LED driver glitch.
2023-11-30 Switch to HID bootloader for smaller footprint and better reliability
2023-11-30 Enabled watchdog timer.
2023-11-30 Quick hack to avoid tripping watchdog when holding down buttons.
